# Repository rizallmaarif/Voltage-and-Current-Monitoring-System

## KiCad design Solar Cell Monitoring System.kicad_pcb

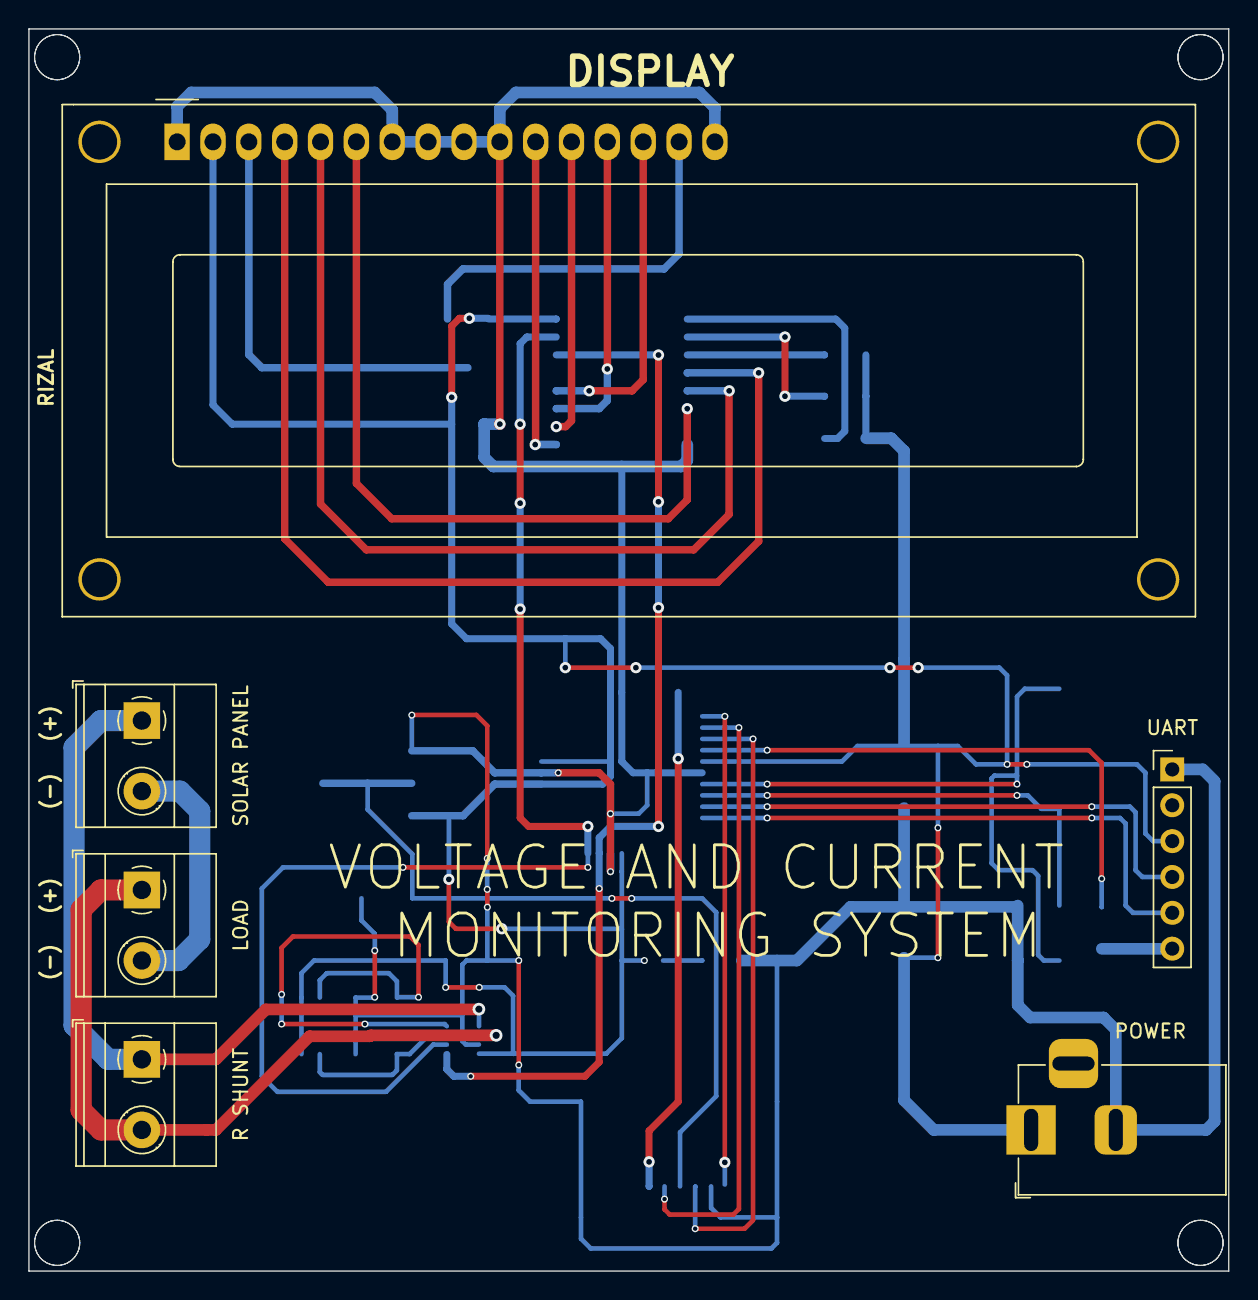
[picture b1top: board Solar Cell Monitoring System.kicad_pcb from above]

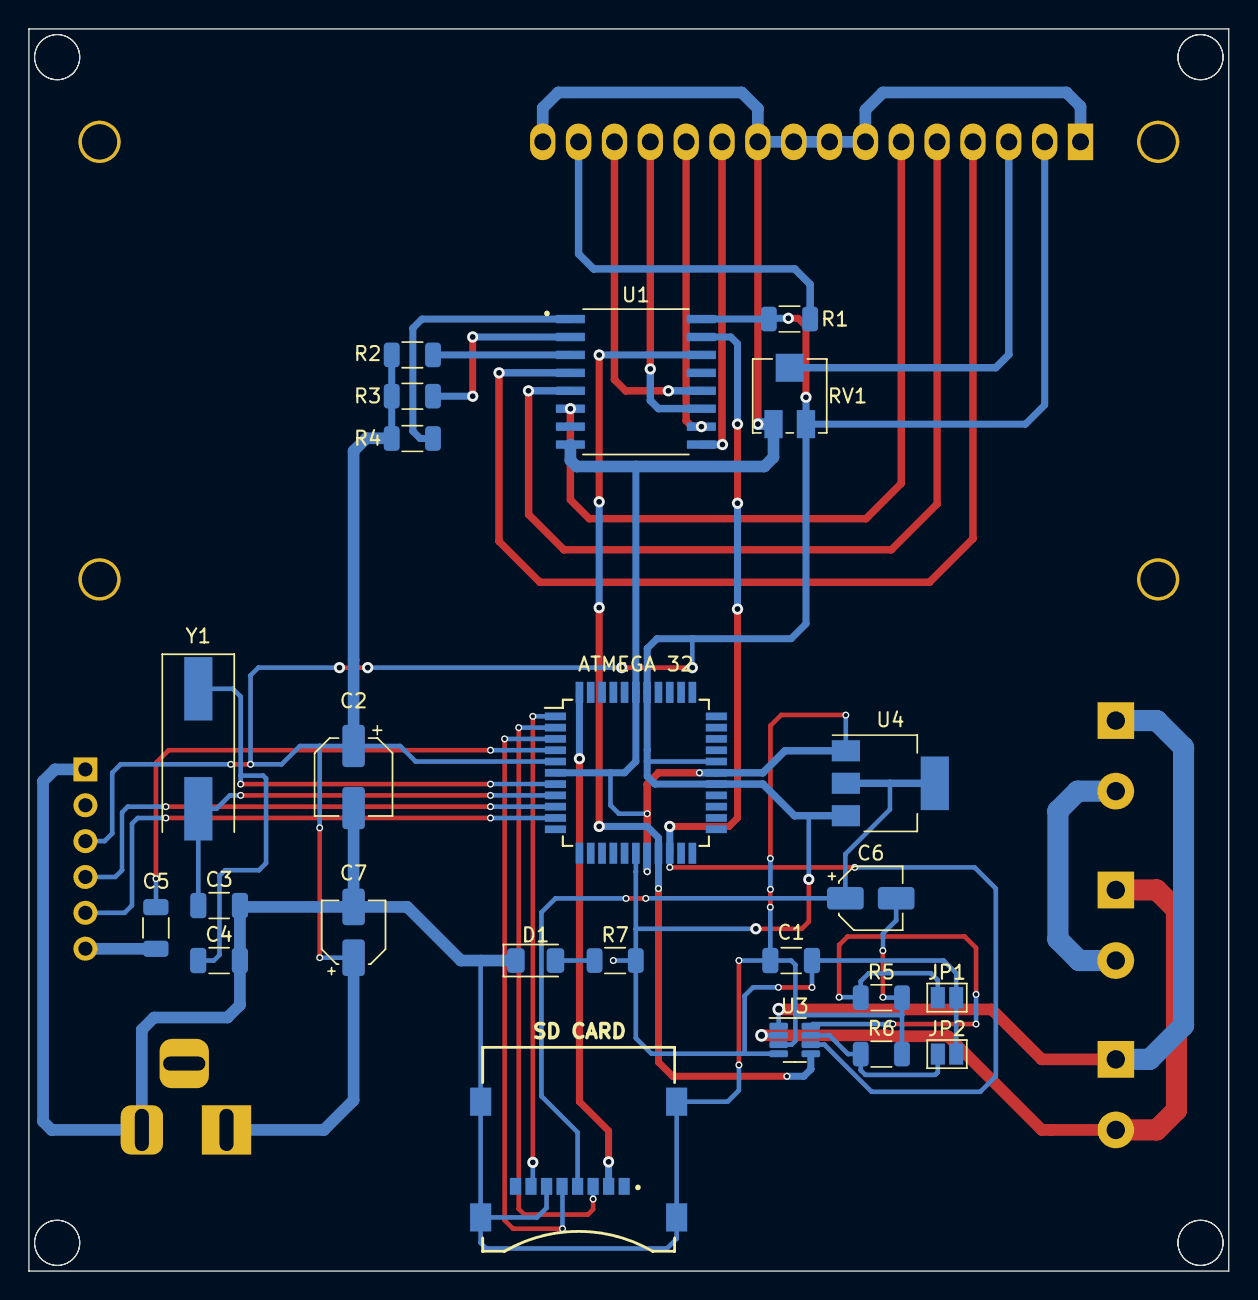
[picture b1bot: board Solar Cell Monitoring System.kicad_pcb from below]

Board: 2 copper layers, 85.0 x 88.0 mm, 30 parts (24 on the bottom side), 33 nets.

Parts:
ATMEGA 32: ATmega32-16A; TQFP-44_10x10mm_P0.8mm
C1: 0.1uF; C_1206_3216Metric
C2: 10uF/25V; CP_Elec_5x5.3
C3, C4: 22pF; C_1206_3216Metric
C5: 100pF; C_1206_3216Metric
C6, C7: 10uF/16V; CP_Elec_4x5.3
D1: LED; LED_1206_3216Metric
DISPLAY: WC1602A
JP1, JP2: Jumper_2_Open; SolderJumper-2_P1.3mm_Open_Pad1.0x1.5mm
LOAD: LOAD; TerminalBlock_Phoenix_MKDS-1,5-2_1x02_P5.00mm_Horizontal
POWER: POWER; BarrelJack_Horizontal
R1: 330; R_1206_3216Metric
R2, R3, R4, R5, R6: 10k; R_1206_3216Metric
R7: 220; R_1206_3216Metric
R SHUNT: R SHUNT(0.001 ohm); TerminalBlock_Phoenix_MKDS-1,5-2_1x02_P5.00mm_Horizontal
RV1: 10k; Potentiometer_Vishay_TS53YJ_Vertical
SD CARD: MEM2067-02-180-00-A_REVB; GCT_MEM2067-02-180-00-A_REVB
SOLAR PANEL: Solar Panel; TerminalBlock_Phoenix_MKDS-1,5-2_1x02_P5.00mm_Horizontal
U1: PCF8574; SOIC127P1030X265-16N
U3: INA219AxDCN; SOT-23-8
U4: AMS1117-3.3; SOT-223-3_TabPin2
UART: T232RL; PinHeader_1x06_P2.54mm_Vertical
Y1: 16MHz; Crystal_SMD_HC49-SD

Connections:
+5V: ATMEGA 32.5 (VCC), ATMEGA 32.17 (VCC), ATMEGA 32.27 (AVCC), ATMEGA 32.29 (AREF), ATMEGA 32.38 (VCC), C1.1, C2.1, C7.1, DISPLAY.2 (VDD), JP1.2 (B), JP2.2 (B), POWER.1, R1.1, R2.1, R3.1, R4.1, R7.2, RV1.1, U1.16 (VCC), U3.4 (VS), U4.3 (VI), UART.3
CS: ATMEGA 32.44 (PB4), SD CARD.2 (CD/DAT3)
GND: ATMEGA 32.6 (GND), ATMEGA 32.18 (GND), ATMEGA 32.28 (GND), ATMEGA 32.39 (GND), C1.2, C2.2, C3.2, C4.2, C6.2, C7.2, D1.1 (K), DISPLAY.1 (VSS), DISPLAY.7 (D0), DISPLAY.8 (D1), DISPLAY.9 (D2), DISPLAY.10 (D3), DISPLAY.16 (LED(-)), POWER.2, R5.2, R6.2, RV1.3, SD CARD.6 (VSS), SD CARD.9 (SHIELD), SD CARD.10 (SHIELD), SD CARD.11 (SHIELD), SD CARD.12 (SHIELD), U1.8 (GND), U3.3 (GND), U4.1 (GND), UART.1
MISO: ATMEGA 32.2 (PB6), SD CARD.3 (CMD)
MOSI: ATMEGA 32.1 (PB5), SD CARD.7 (DAT0)
unnamed: D1.2 (A), R7.1
unnamed: DISPLAY.11 (D4), U1.9 (P4)
unnamed: DISPLAY.12 (D5), U1.10 (P5)
unnamed: DISPLAY.13 (D6), U1.11 (P6)
unnamed: DISPLAY.14 (D7), U1.12 (P7)
unnamed: DISPLAY.6 (E), U1.6 (P2)
unnamed: DISPLAY.15 (LED(+)), R1.2
unnamed: DISPLAY.4 (RS), U1.4 (P0)
unnamed: DISPLAY.5 (R/W), U1.5 (P1)
unnamed: DISPLAY.3 (VO), RV1.2
unnamed: R SHUNT.1, SOLAR PANEL.1, U3.1 (IN+)
unnamed: LOAD.1, R SHUNT.2, U3.2 (IN-)
unnamed: LOAD.2, SOLAR PANEL.2
unnamed: ATMEGA 32.9 (PD0), UART.4
unnamed: ATMEGA 32.10 (PD1), UART.5
unnamed: C5.1, UART.6
unnamed: C6.1, SD CARD.4 (VDD), U4.2 (VO)
unnamed: JP1.1 (A), R5.1, U3.8 (A1)
unnamed: JP2.1 (A), R6.1, U3.7 (A0)
unnamed: R4.2, U1.1 (A0)
unnamed: R3.2, U1.2 (A1)
unnamed: R2.2, U1.3 (A2)
unnamed: ATMEGA 32.8 (XTAL1), C3.1, Y1.2
unnamed: ATMEGA 32.7 (XTAL2), C4.1, Y1.1
RESET: ATMEGA 32.4 (~RESET), C5.2
SCK: ATMEGA 32.3 (PB7), SD CARD.5 (CLK)
SCL(INA219): ATMEGA 32.19 (PC0), U1.14 (SCL), U3.5 (SCL)
SDA(INA219): ATMEGA 32.20 (PC1), U1.15 (SDA), U3.6 (SDA)
